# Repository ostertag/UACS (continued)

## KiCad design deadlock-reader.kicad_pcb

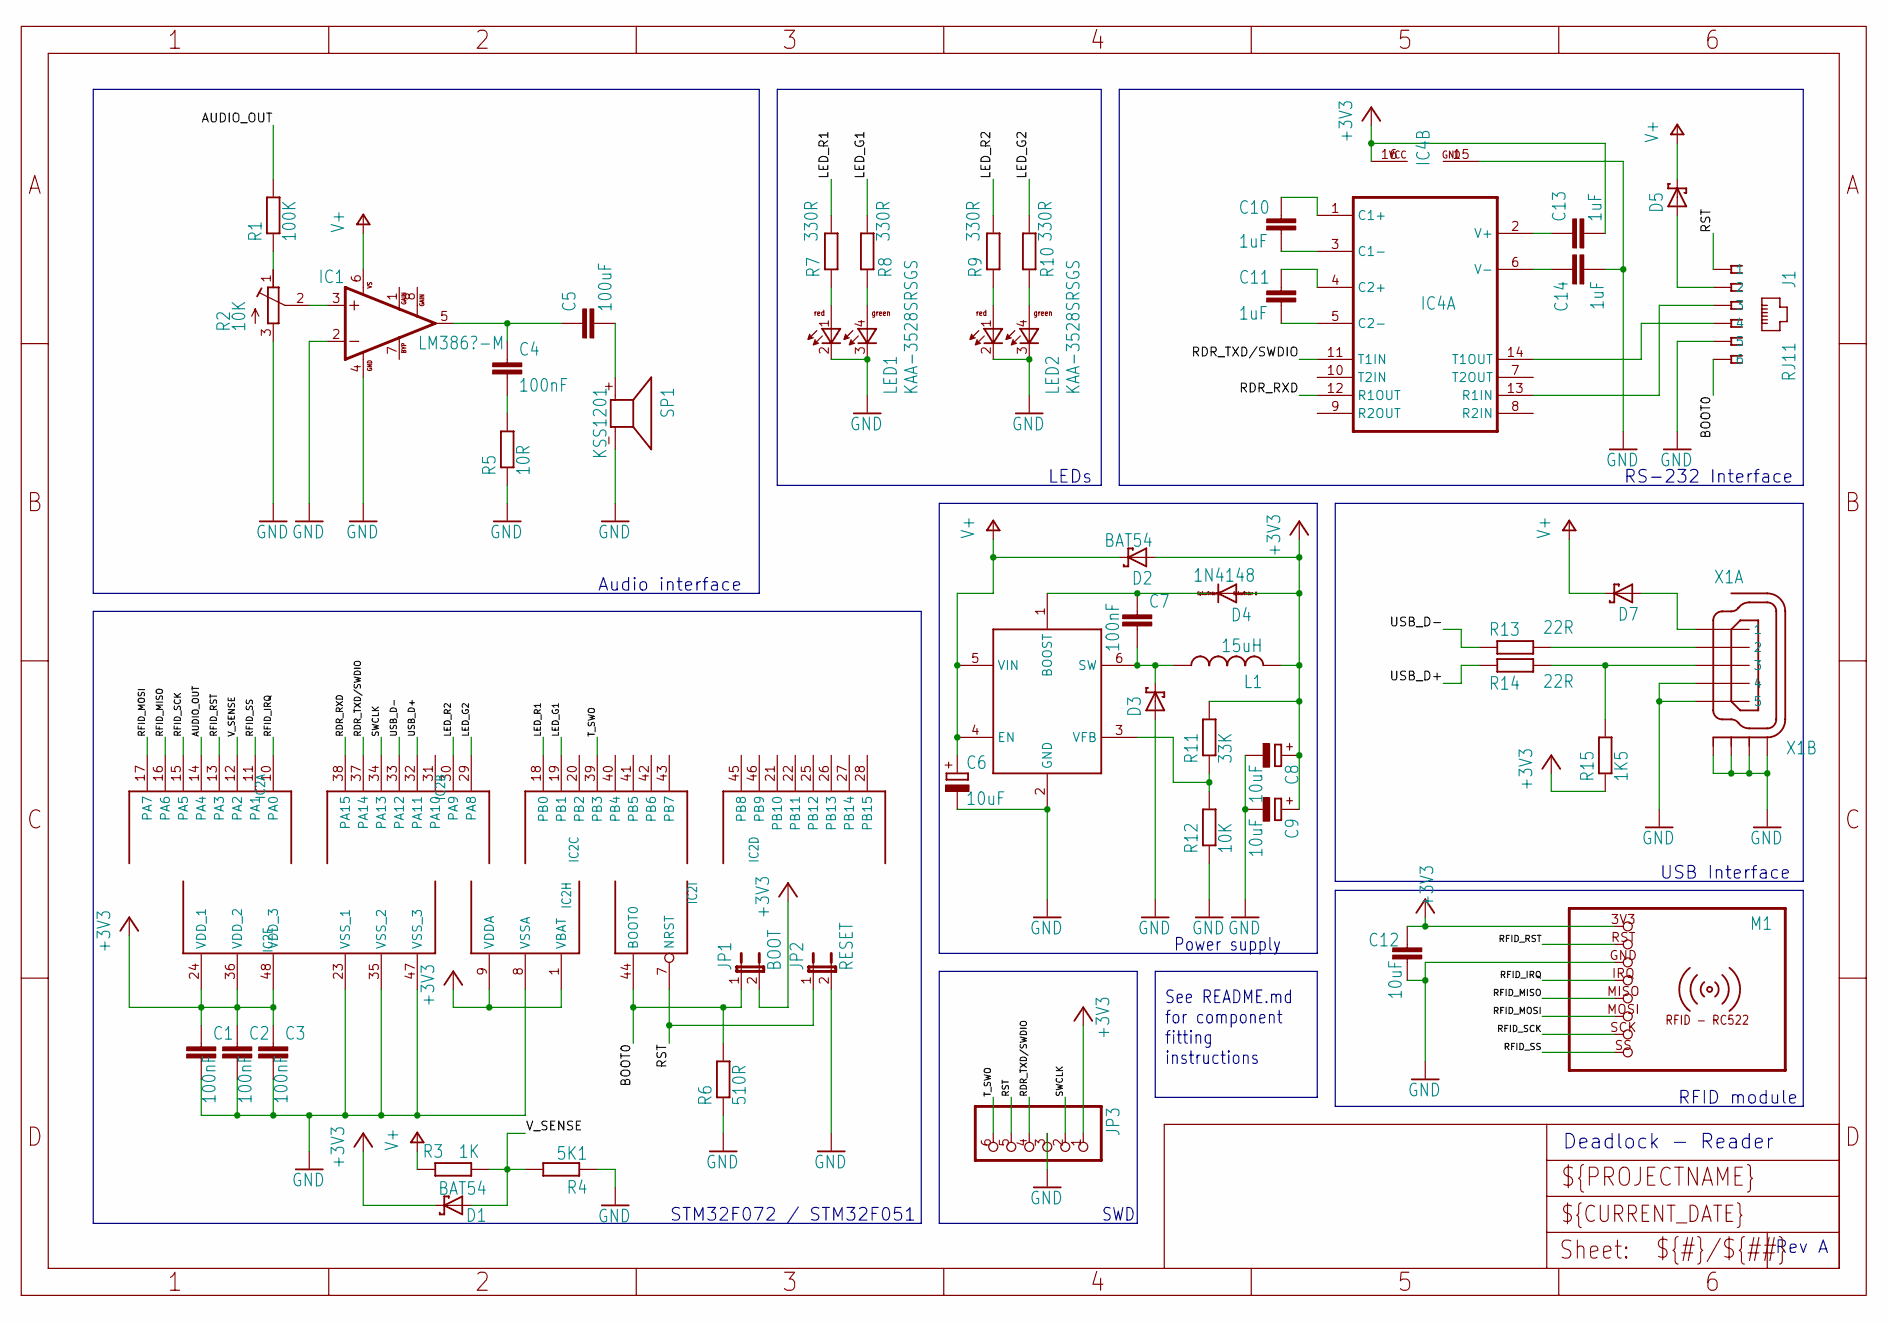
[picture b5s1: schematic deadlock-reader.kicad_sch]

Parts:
C1, C2, C3, C4, C7: 100nF; C0805
C5: 100uF; C1206
C6: 10uF; SMC_D
C8, C9: 10uF; A_3216-18R
C10, C11, C13, C14: 1uF; C0805
C12: 10uF; C0805
D1, D2: BAT54; SOT23
D3, D5, D7: BAT60J; SOD323_ST
D4: 1N4148; SOD323-W
IC1: LM386?-M; SO08
IC2: STM32F072XX; TQFP48
IC3: MCP16301/H; SOT23-6
IC4: MAX3232SE; SO16
J1: RJ11; RJ11-NO_SHIELD
JP1: BOOT; JP1
JP2: RESET; JP1
JP3: PINHD-1X6; 1X06
L1: 15uH; PIS2816
LED1, LED2: KAA-3528SRSGS
M1: RFID-RC522
R1: 100K; M0805
R2: 10K; RTRIM3314G
R3: 1K; R0805
R4: 5K1; R0805
R5: 10R; R0805
R6: 510R; R0805
R7, R8, R9, R10: 330R; R0805
R11: 33K; R0805
R12: 10K; R0805
R13, R14: 22R; R0805
R15: 1K5; R0805
SP1: KSS1201
X1: MINI-USB-SCHIELD-32005-301; 32005-301

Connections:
+3V3: C1.1, C2.1, C3.1, C8.+, C9.+, C12.1, C13.2, D1.3 (C), D2.1 (A), D4.A, IC2.1 (VBAT), IC2.9 (VDDA), IC2.24 (VDD_1), IC2.36 (VDD_2), IC2.48 (VDD_3), IC4.16 (VCC), JP1.2, JP3.1, L1.2, M1.3V3 (1), R11.2, R15.1
/AUDIO_OUT: IC2.14 (PA4), R1.2
/BOOT0: IC2.44 (BOOT0), J1.6, JP1.1, R6.2
/LED_G1: IC2.19 (PB1), R8.2
/LED_G2: IC2.29 (PA8), R10.2
/LED_R1: IC2.18 (PB0), R7.2
/LED_R2: IC2.30 (PA9), R9.2
/RDR_RXD: IC2.38 (PA15), IC4.12 (R1OUT)
/RDR_TXD/SWDIO: IC2.37 (PA14), IC4.11 (T1IN), JP3.4
/RFID_IRQ: IC2.10 (PA0), M1.IRQ (4)
/RFID_MISO: IC2.16 (PA6), M1.MISO (5)
/RFID_MOSI: IC2.17 (PA7), M1.MOSI (6)
/RFID_RST: IC2.13 (PA3), M1.RST (2)
/RFID_SCK: IC2.15 (PA5), M1.SCK (7)
/RFID_SS: IC2.11 (PA1), M1.SS (8)
/RST: IC2.7 (NRST), J1.1, JP2.1, JP3.5
/SWCLK: IC2.34 (PA13), JP3.2
/T_SWO: IC2.39 (PB3), JP3.6
/USB_D+: IC2.32 (PA11), R14.1
/USB_D-: IC2.33 (PA12), R13.1
/V_SENSE: D1.1 (A), IC2.12 (PA2), R3.1, R4.2
GND: C1.2, C2.2, C3.2, C6.-, C8.-, C9.-, C12.2, C14.2, D3.A, IC1.2 (-IN), IC1.4 (GND), IC2.8 (VSSA), IC2.23 (VSS_1), IC2.35 (VSS_2), IC2.47 (VSS_3), IC3.2 (GND), IC4.15 (GND), J1.5, JP2.2, JP3.3, LED1.2 (C-RED), LED1.3 (C-GREEN), LED2.2 (C-RED), LED2.3 (C-GREEN), M1.GND (3), R2.3 (A), R4.1, R5.1, R6.1, R12.1, SP1.- (2), X1.4, X1.5, X1.M1 (S1), X1.M2 (S2), X1.M3 (S3), X1.M4 (S4)
unnamed: C4.2, R5.2
unnamed: D5.A, J1.2
unnamed: D7.A, X1.1
unnamed: IC1.3 (+IN), R2.2 (S)
unnamed: C4.1, C5.1, IC1.5 (OUT)
unnamed: C7.1, D4.C, IC3.1 (BOOST)
unnamed: C7.2, D3.C, IC3.6 (SW), L1.1
unnamed: IC3.3 (VFB), R11.1, R12.2
unnamed: C10.1, IC4.1 (C1+)
unnamed: C10.2, IC4.3 (C1-)
unnamed: C11.1, IC4.4 (C2+)
unnamed: C11.2, IC4.5 (C2-)
unnamed: IC4.13 (R1IN), J1.3
unnamed: IC4.14 (T1OUT), J1.4
unnamed: C13.1, IC4.2 (V+)
unnamed: C14.1, IC4.6 (V-)
unnamed: LED1.4 (A-GREEN), R8.1
unnamed: LED1.1 (A-RED), R7.1
unnamed: LED2.4 (A-GREEN), R10.1
unnamed: LED2.1 (A-RED), R9.1
unnamed: R1.1, R2.1 (E)
unnamed: R13.2, X1.2
unnamed: R14.2, R15.2, X1.3
unnamed: C5.2, SP1.+ (1)
V+: C6.+, D2.3 (C), D5.C, D7.C, IC1.6 (VS), IC3.4 (EN), IC3.5 (VIN), R3.2

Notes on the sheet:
Audio interface
SWD
Rev A
RFID module
RS-232 Interface
Deadlock - Reader
See README.md for component fitting instructions
Power supply
STM32F072 / STM32F051
USB Interface
LEDs

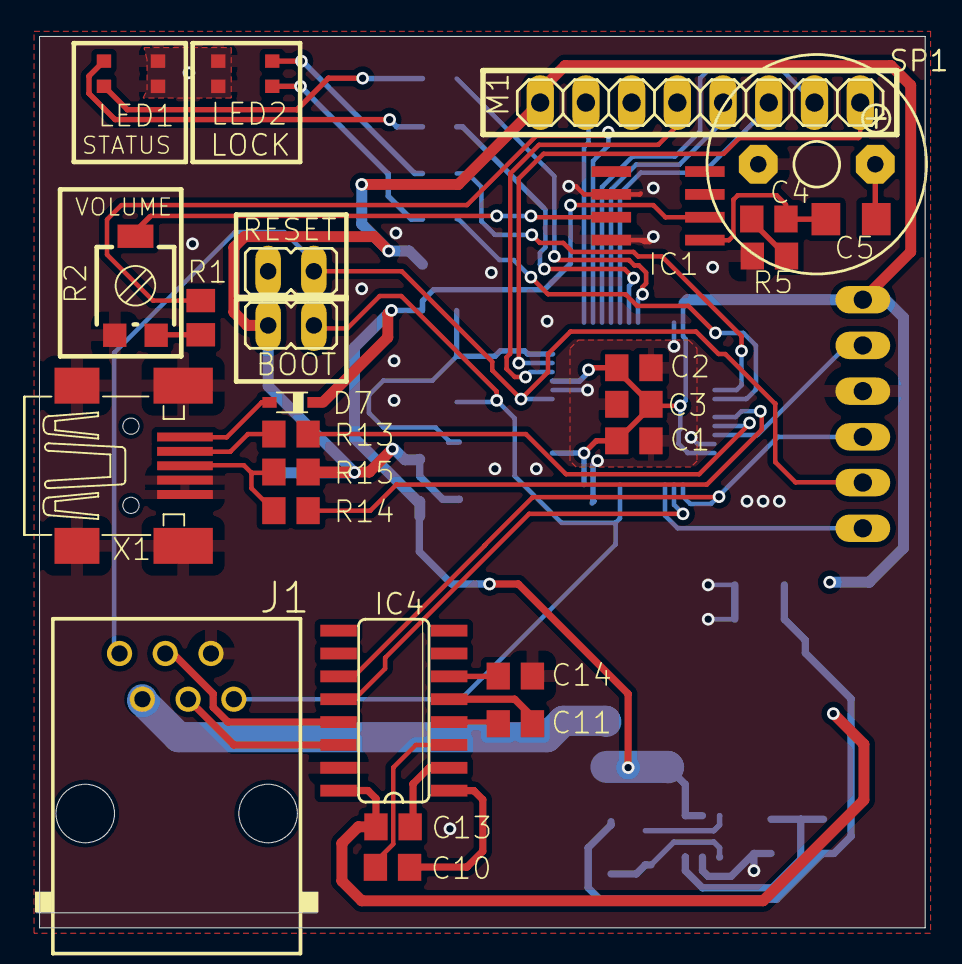
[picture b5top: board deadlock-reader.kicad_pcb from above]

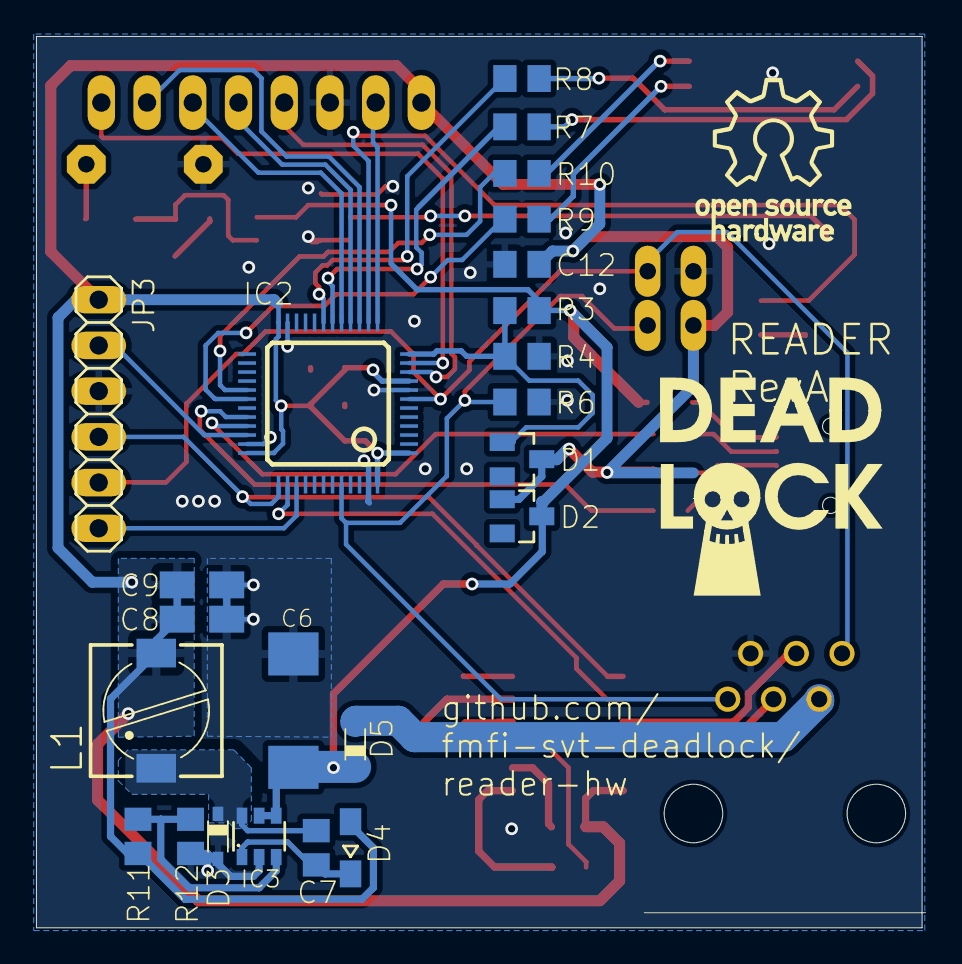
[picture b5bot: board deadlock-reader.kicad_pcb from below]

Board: 2 copper layers, 49.2 x 49.5 mm, 49 parts (23 on the bottom side), 47 nets.

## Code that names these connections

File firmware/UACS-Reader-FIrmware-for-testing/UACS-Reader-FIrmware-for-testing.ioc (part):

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Mcu.Name=STM32F103C(8-B)Tx
Mcu.Package=LQFP48
Mcu.UserName=STM32F103C8Tx
PA11.Mode=Device
PA11.Signal=USB_DM
PA12.Mode=Device
PA12.Signal=USB_DP
PA13.Mode=Trace_Asynchronous_SW
PA13.Signal=SYS_JTMS-SWDIO
PA14.Mode=Trace_Asynchronous_SW
PA14.Signal=SYS_JTCK-SWCLK
PA3.GPIOParameters=GPIO_Label
PA3.GPIO_Label=RFID_IRQ
PA3.Signal=GPIO_Input
PA4.GPIOParameters=GPIO_Label
PA4.GPIO_Label=RFID_SDA
PA4.Signal=GPIO_Output
PA5.GPIOParameters=GPIO_Label
PA5.GPIO_Label=RFID_SCK
PA5.Mode=Full_Duplex_Master
PA5.Signal=SPI1_SCK
PA6.GPIOParameters=GPIO_Label
PA6.GPIO_Label=RFID_MISO
PA6.Mode=Full_Duplex_Master
PA6.Signal=SPI1_MISO
PA7.GPIOParameters=GPIO_Label
PA7.GPIO_Label=RFID_MOSI
PA7.Mode=Full_Duplex_Master
PA7.Signal=SPI1_MOSI
PA8.GPIOParameters=GPIO_Label
PA8.GPIO_Label=LED_R2
PA8.Signal=GPIO_Output
PA9.GPIOParameters=GPIO_Label
PA9.GPIO_Label=LED_G2
PA9.Signal=GPIO_Output
PB0.GPIOParameters=GPIO_Label
PB0.GPIO_Label=RFID_RST
PB0.Signal=GPIO_Output
PB10.Mode=Asynchronous
PB10.Signal=USART3_TX
PB11.Mode=Asynchronous
PB11.Signal=USART3_RX
PB3.Mode=Trace_Asynchronous_SW
PB3.Signal=SYS_JTDO-TRACESWO
PB4.GPIOParameters=GPIO_Label
PB4.GPIO_Label=AUDIO_OUT
PB4.Signal=S_TIM3_CH1
PB6.GPIOParameters=GPIO_Label
PB6.GPIO_Label=LED_R1
PB6.Signal=GPIO_Output
PB7.GPIOParameters=GPIO_Label
PB7.GPIO_Label=LED_G1
PB7.Signal=GPIO_Output
PD0-OSC_IN.Mode=HSE-External-Oscillator
PD0-OSC_IN.Signal=RCC_OSC_IN
PD1-OSC_OUT.Mode=HSE-External-Oscillator
PD1-OSC_OUT.Signal=RCC_OSC_OUT
RCC.HSEDivPLL=RCC_HSE_PREDIV_DIV2
RCC.HSE_VALUE=16000000
RCC.SYSCLKFreq_VALUE=72000000
RCC.SYSCLKSource=RCC_SYSCLKSOURCE_PLLCLK
board=custom

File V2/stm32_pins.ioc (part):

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Mcu.Name=STM32H523CETx
Mcu.Package=LQFP48
Mcu.UserName=STM32H523CETx
PA11.Mode=Device
PA11.Signal=USB_DM
PA12.Mode=Device
PA12.Signal=USB_DP
PA13(JTMS/SWDIO).Mode=Trace_Asynchronous_SW
PA13(JTMS/SWDIO).Signal=DEBUG_JTMS-SWDIO
PA14(JTCK/SWCLK).Mode=Trace_Asynchronous_SW
PA14(JTCK/SWCLK).Signal=DEBUG_JTCK-SWCLK
PA15(JTDI).GPIOParameters=GPIO_Label
PA15(JTDI).GPIO_Label=LED_R1
PA15(JTDI).Signal=GPIO_Output
PA3.Mode=Half_Duplex_Master_Tx
PA3.Signal=I2S2_WS
PA4.GPIOParameters=GPIO_Label,GPIO_ModeDefaultOutputPP
PA4.GPIO_Label=SPEAKER_ON/OFF\!
PA4.GPIO_ModeDefaultOutputPP=GPIO_MODE_OUTPUT_PP
PA4.Signal=GPIO_Output
PA5.Mode=Full_Duplex_Master
PA5.Signal=SPI1_SCK
PA6.Mode=Full_Duplex_Master
PA6.Signal=SPI1_MISO
PA7.Mode=Full_Duplex_Master
PA7.Signal=SPI1_MOSI
PB0.GPIOParameters=GPIO_Speed,PinState,GPIO_Label
PB0.GPIO_Label=SD_SS
PB0.GPIO_Speed=GPIO_SPEED_FREQ_HIGH
PB0.PinState=GPIO_PIN_SET
PB0.Signal=GPIO_Output
PB1.GPIOParameters=GPIO_Label
PB1.GPIO_Label=SD_Detected
PB1.Signal=GPIO_Input
PB10.GPIOParameters=PinState,GPIO_Label
PB10.GPIO_Label=RFID_RST
PB10.PinState=GPIO_PIN_SET
PB10.Signal=GPIO_Output
PB13.Signal=GPXTI13
PB14.GPIOParameters=GPIO_Speed,PinState,GPIO_Label
PB14.GPIO_Label=RFID_SS
PB14.GPIO_Speed=GPIO_SPEED_FREQ_MEDIUM
PB14.PinState=GPIO_PIN_SET
PB14.Signal=GPIO_Output
PB15.Mode=Half_Duplex_Master_Tx
PB15.Signal=I2S2_SDO
PB2.Mode=Half_Duplex_Master_Tx
PB2.Signal=I2S2_CK
PB3(JTDO/TRACESWO).Mode=Trace_Asynchronous_SW
PB3(JTDO/TRACESWO).Signal=DEBUG_JTDO-SWO
PB4(NJTRST).GPIOParameters=GPIO_Label
PB4(NJTRST).GPIO_Label=LED_G1
PB4(NJTRST).Signal=GPIO_Output
PB5.GPIOParameters=GPIO_Label
PB5.GPIO_Label=LED_R2
PB5.Signal=GPIO_Output
PB6.GPIOParameters=GPIO_Label
PB6.GPIO_Label=LED_G2
PB6.Signal=GPIO_Output
PB7.Mode=FDCAN_Activate
PB7.Signal=FDCAN1_TX
PB8.Mode=FDCAN_Activate
PB8.Signal=FDCAN1_RX
PH0-OSC_IN(PH0).Mode=HSE-External-Oscillator
PH0-OSC_IN(PH0).Signal=RCC_OSC_IN
PH1-OSC_OUT(PH1).Mode=HSE-External-Oscillator
PH1-OSC_OUT(PH1).Signal=RCC_OSC_OUT
RCC.HSE_VALUE=25000000
RCC.SYSCLKFreq_VALUE=32000000
board=custom

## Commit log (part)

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2024-06-09 Rename 20005004D.pdf to Data_sheet.pdf
2024-06-09 Rename Data_sheet.pdf to Data_sheet.pdf
2024-06-14 Rename MAX3222-MAX3241.pdf to Data_sheet.pdf
2024-06-15 Rename reader_kozuch.kicad_pcb to power_suplly_rs232_interface_kozuch.kicad_pcb
2024-06-15 Rename reader_kozuch.kicad_pro to power_suplly_rs232_interface_kozuch.kicad_pro
2024-06-15 Rename reader_kozuch.kicad_sch to power_suplly_rs232_interface_kozuch.kicad_sch
2024-07-14 Rename README to README.md
2025-02-23 Create connection_to_PCB
2025-02-23 Update connection_to_PCB
2025-02-24 updating stm32
2025-02-24 small tweaks
2025-02-25 adding rc522
2025-03-01 updated stm32_interface
2025-03-04 minor changes
2025-03-22 adding schematics and board of whole_reader
2025-03-22 minor changes in pcb layout
2025-03-25 updates of physical_board
2025-04-01 updates of board
2025-04-01 updating pcb
2025-04-01 updating schematic
2025-04-01 updated pcb
2025-04-01 remove lck files
2025-04-01 trying adding solder pads
2025-04-02 updating footprint
2025-04-05 new gerber files and updates to pcb
2025-04-05 Úprava PCB a schémy zapojenia
2025-04-07 updates to pcb and added some 3d models
2025-04-07 minor tweaks on board
2025-04-08 Úprava PCB
2025-04-08 added button for reseting
2025-04-08 changed speaker symbol and footprint
2025-04-08 Upravy PCB
2025-04-08 updated holes for speaker
2025-04-08 updated speaker schematic
2025-04-09 Added toplayer ground copper pour
2025-04-10 RST -> NRST, BOOT -> BOOT0, popis pre SWD
2025-04-10 Oprava pre PWR_FLAG, doplnenie dátumu a revízie
2025-04-10 Drobné úpravy rozloženia schémy
2025-04-11 changed notation of some components
2025-04-11 viring diferential pair
2025-04-14 wired diferential pair on usb
2025-04-14 excluded rc522 card and speaker from bom file
2025-04-14 Pridanie testovacích bodov
2025-04-15 Add netclasses
2025-04-15 added skelet of bc thesis file
2025-04-15 Úprava schémy
2025-04-15 Add jumper for audio
2025-04-15 Netclass Power and GND track width set to 3.0 mm
2025-04-15 Rozšírenie GND výplne na niektorých miestach
2025-04-15 Pridanie slzičiek
2025-04-16 Drobná úprava schémy (zarovnanie kondenzátorov a popisov)
2025-04-16 Úprava GND výplne, netclass a šírky niektorých spojov
2025-04-16 changed diodes
2025-04-16 added new diodes
2025-04-16 Úprava rozloženia dosky a pridanie TP5 pre RFID_IRQ
2025-04-16 Pridane checkbox Tested
2025-04-17 Pridanie loga
2025-04-17 Pridanie LCSC, JLSPCB, úprava TP
2025-04-17 Uzavretie GND okolo USB-C
2025-04-17 Pridaný dátový list a PN pre oscilátor
2025-04-21 STM32 datasheet, drobné úpravy PCB
2025-04-21 Rerouting of AUDIO_OUT and LEDs, change of associated PINs on STM32
    AUDIO_OUT: 42 -> 40
    LED_G1: 28 -> 29 -> 43
    LED_R1: 30 -> 30 -> 42
    LED_G2: 11 -> 43 -> 30
    LED_R2: 12 -> 42 -> 29
2025-04-22 Drobné úpravy
    - pridanie linky na ST.com stránku k MCU
    - pridanie označenia polohy prepínača v režime Boot
    - pridanie popiskov LED na vrchnú stranu
2025-04-22 Použitie projektových premenných, nastavenie netclass farieb pre schému
2025-04-22 Pridanie 3D modelu pre LED
2025-04-22 Drobné úpravy popisov zosilňovača
2025-04-22 Otočenie potenciometra a pridanie smeru otáčania
2025-04-23 Prvá verzia panelizácie
2025-04-23 Oprava skriptu a zmena panela na 3x2
2025-04-23 Úprava panelizácie
2025-04-24 Doplnenie dátových listov a TP sú mimo BOM
2025-04-24 updates on pcb, bom file and experimenting with footprints
2025-04-25 Úprava popisov
2025-04-25 Otočenie potenciometra
2025-04-27 Posunutie USB-C konektora na kraj PCB podľa vyznačenej čiary
2025-04-27 updated values and footprints of rezistors and other parts
2025-04-28 add some vias
2025-04-29 added speaker to the schematics
2025-04-29 moved rj 12 connector
2025-04-29 changed rotations of components
2025-04-29 dorbné úpravy PCB
2025-04-29 úprava RJ12
2025-04-30 drobné úpravy schémy
2025-05-01 added new conector for sp and low pass filter
2025-05-04 pridanie LTspice modelu konverzie PWM na audio a jeho implementácia na PCB
2025-05-05 added part numbers and datasheets to components
2025-05-05 potenciometer 5k
2025-05-05 changed potentiometer footprint, datasheet etc...
2025-05-06 changed sp_conn
2025-05-06 changed 3d models
2025-05-06 drobné úpravy
2025-05-28 uploaded project for cube ide
2025-05-29 changing versioning
2025-05-29 adding skelet of firmware
2025-05-29 added blinking diodes and pwm signal modulation
2025-05-30 added simple program for testing periferals
2025-05-31 added testing script, with simple cli
2026-03-11 kicad upgrade added undefined_netclass parameter
2026-04-23 - added audio ampliefier for i2s(removed old i2c circuit). - added sd card reader. - changed stm32 model. - RS232 transciever -> FDCAN transciever
    --- cleaned schematic a little
2026-04-23 kicad 9 -> 10
2026-04-23 added .gitatributes to force LF files. added ethernet connecotr , not yet connected
2026-04-23 connected ethernet cable. counting with CAT5 configuration
2026-04-23 changed ignore
2026-04-23 removed .history for making problems
2026-05-04 cleaning and pin change in progress
2026-05-05 cleaned scheamtic. wired correct pins of mcu... their selection is in the stm32 selector
2026-05-05 .history ... deleted
2026-05-05 hopefully fixed the .history of kicad 10
2026-05-06 Cleaned schematic and removed RFID_IRQ pin
2026-05-07 small schema changes
2026-05-07 combined spi's to only one. now we have traceswo for debug. added some resistors and caps. changes some pin locations. added rfid_irq to mcu for detection added README.md
2026-05-20 done most of todo + proposed switch desing for changing volume of speaker
2026-05-23 discussed changes and speaker connector
2026-06-04 in process of making pcb
2026-06-04 pcb propably dones
2026-06-05 changed debug connector to male, fixed 3d models not showing, moved sdcard slot invards by 2.3mm
2026-06-05 closed kicad... removed locks
2026-06-09 final touches
2026-06-09 added switch combination table at the back, swapped 2 positions of SW1... X <-> 100K so it better fits pcb
2026-06-09 added fiducials
2026-06-10 small changes... stm32 pins in cubemx set based on schematic.
2026-06-10 changed signage in gain slot table
2026-06-10 fixed errors in board check: courtyard overlaps with fiducials
2026-06-11 chore: small PCB layout changes
2026-06-11 changed 20mA led to 2mA led so both are same. changed orientation of card logo on back of board
2026-06-11 changed led red color resistor from 560 to 787
2026-06-11 changed size of pcb paper to A5 added labels and groups to schematic
2026-06-12 changed few components because of availability. moved thesis into this repository.
2026-06-13 changed few things... 1.1.2 text, 1.5 table content, updated few reference links
2026-06-13 updated documentation and Latex
2026-06-13 added formula for calculating C1 and C2
2026-06-13 small update
2026-06-14 updated pdf with better images of pcb
